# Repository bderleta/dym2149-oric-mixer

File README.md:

# dym2149-oric-mixer
Oric mixer board for [Dual YM2149 synth](https://github.com/bderleta/dym2149-board). 
Loosely based on [Oric Atmos schematic](https://www.986-studio.com/wp-content/uploads/2014/09/OricSchematics.pdf). Can be used as a kind of reference for creating own mixers.

Beware: Capacitor values and footprints are wrong!

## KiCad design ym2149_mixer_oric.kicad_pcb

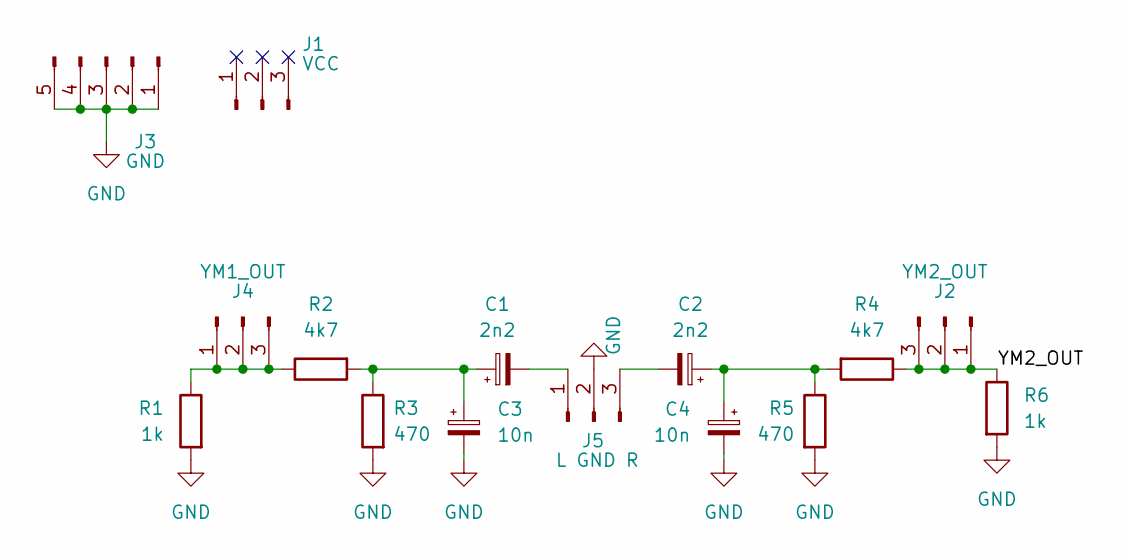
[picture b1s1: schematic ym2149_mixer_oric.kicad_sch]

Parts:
C1, C2: 2n2; CP_Radial_D5.0mm_P2.50mm
C3, C4: 10n; CP_Radial_D5.0mm_P2.50mm
J1: VCC; PinSocket_1x03_P2.54mm_Vertical
J2: YM2_OUT; PinSocket_1x03_P2.54mm_Vertical
J3: GND; PinSocket_1x05_P2.54mm_Vertical
J4: YM1_OUT; PinSocket_1x03_P2.54mm_Vertical
J5: L GND R; PinSocket_1x03_P2.54mm_Vertical
R1, R6: 1k; R_Axial_DIN0207_L6.3mm_D2.5mm_P10.16mm_Horizontal
R2, R4: 4k7; R_Axial_DIN0207_L6.3mm_D2.5mm_P10.16mm_Horizontal
R3, R5: 470; R_Axial_DIN0207_L6.3mm_D2.5mm_P10.16mm_Horizontal

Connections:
/YM2_OUT: J2.1, J2.2, J2.3, R4.1, R6.1
GND: C3.2, C4.2, J3.1, J3.2, J3.3, J3.4, J3.5, J5.2, R1.2, R3.2, R5.2, R6.2
unnamed: C1.1, C3.1, R2.2, R3.1
unnamed: C2.1, C4.1, R4.2, R5.1
unnamed: J4.1, J4.2, J4.3, R1.1, R2.1
unnamed: C1.2, J5.1
unnamed: C2.2, J5.3

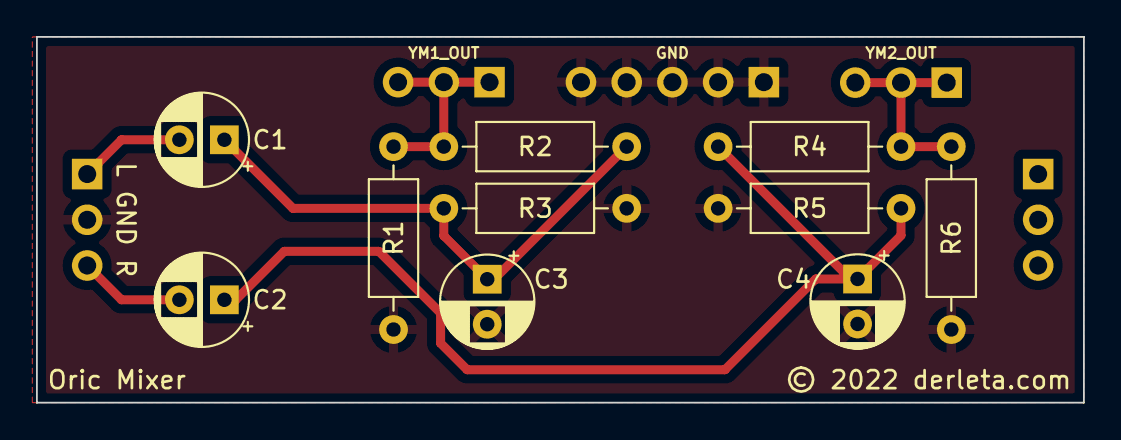
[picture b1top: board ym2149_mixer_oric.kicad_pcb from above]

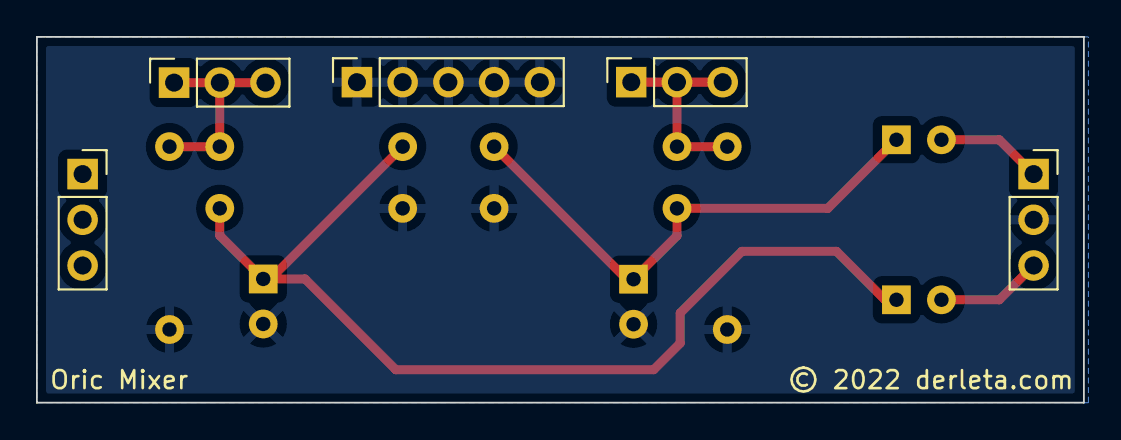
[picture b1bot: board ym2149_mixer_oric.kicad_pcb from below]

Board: 2 copper layers, 58.2 x 20.3 mm, 15 parts (5 on the bottom side), 7 nets.

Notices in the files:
ym2149_mixer_oric.kicad_pcb:
© 2022 derleta.com
